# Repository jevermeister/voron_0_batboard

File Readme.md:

# Batboard

The batboard is a passive tool board mounting on the back of the MiniAB pancake 
stepper of the Voron 0.1. The board solidly mounts with 20mm brass standoffs to the 
back of the mini after burner mounting screws and provides JST PH connectors 
(2mm pitch) for the two part cooling fans, the hotend fan, a 4-pin thermistor, 
two switches (for example the X endstop + a klicky probe) as well as the stepper and a chamber thermistor. 
The heater output is provided as a 2x1 Molex Microfit connector and all terminals 
are terminated onto a 2x9 Microfit.

# BOM

For the PCB:
- 1x Molex 43045-1800 (Microfit 2x9) 
- 1x Molex 43045-0200 (Microfit 2x1)
- 3x JST PH 2 Pin, B2B-PH-K-S(LF)(SN)
- 3x JST PH 3 Pin, B3B-PH-K-S(LF)(SN)
- 2x JST PH 4 Pin, B4B-PH-K-S(LF)(SN)
- MF58 3950 thermistor

And the appropriate connectors for your cable loom...

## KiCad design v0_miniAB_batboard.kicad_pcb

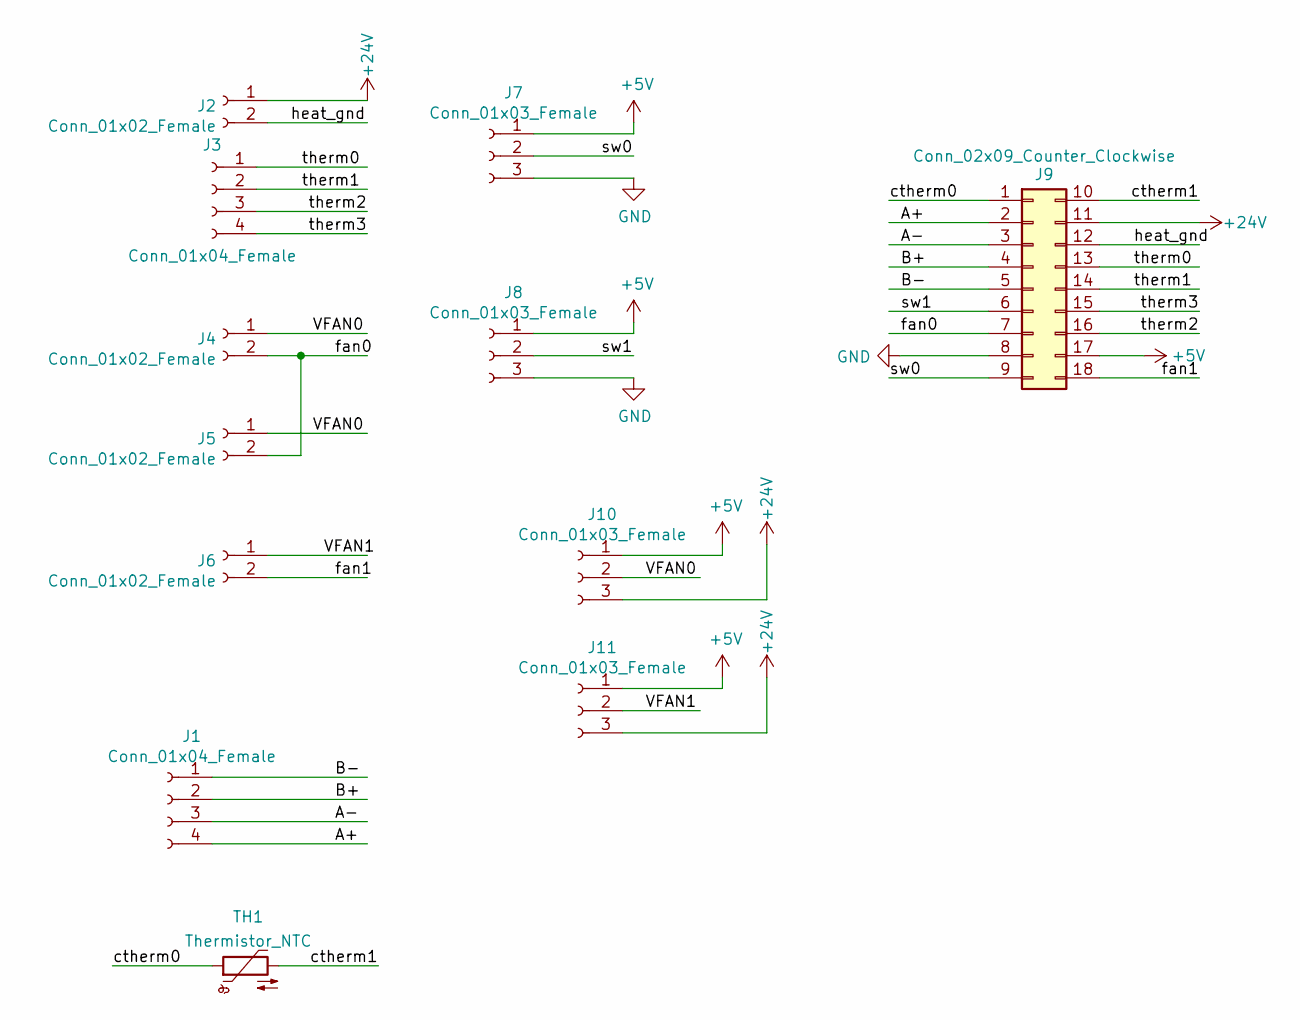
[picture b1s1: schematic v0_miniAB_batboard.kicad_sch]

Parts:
J1, J3: Conn_01x04_Female; JST_PH_B4B-PH-K_1x04_P2.00mm_Vertical
J2: Conn_01x02_Female; Molex_Micro-Fit_3.0_43045-0200_2x01_P3.00mm_Horizontal
J4, J5, J6: Conn_01x02_Female; JST_PH_B2B-PH-K_1x02_P2.00mm_Vertical
J7, J8: Conn_01x03_Female; JST_PH_B3B-PH-K_1x03_P2.00mm_Vertical
J9: Conn_02x09_Counter_Clockwise; Molex_Micro-Fit_3.0_43045-1800_2x09_P3.00mm_Horizontal
J10, J11: Conn_01x03_Female; SolderJumper-3_P1.3mm_Bridged12_RoundedPad1.0x1.5mm_NumberL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
TH1: Thermistor_NTC; R_Axial_DIN0204_L3.6mm_D1.6mm_P7.62mm_Horizontal

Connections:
+5V: J7.1, J8.1, J9.17, J10.1, J11.1
+24V: J2.1, J9.11, J10.3, J11.3
/A+: J1.4, J9.2
/A-: J1.3, J9.3
/B+: J1.2, J9.4
/B-: J1.1, J9.5
/VFAN0: J4.1, J5.1, J10.2
/VFAN1: J6.1, J11.2
/ctherm0: J9.1, TH1.1
/ctherm1: J9.10, TH1.2
/fan0: J4.2, J5.2, J9.7
/fan1: J6.2, J9.18
/heat_gnd: J2.2, J9.12
/sw0: J7.2, J9.9
/sw1: J8.2, J9.6
/therm0: J3.1, J9.13
/therm1: J3.2, J9.14
/therm2: J3.3, J9.16
/therm3: J3.4, J9.15
GND: J7.3, J8.3, J9.8

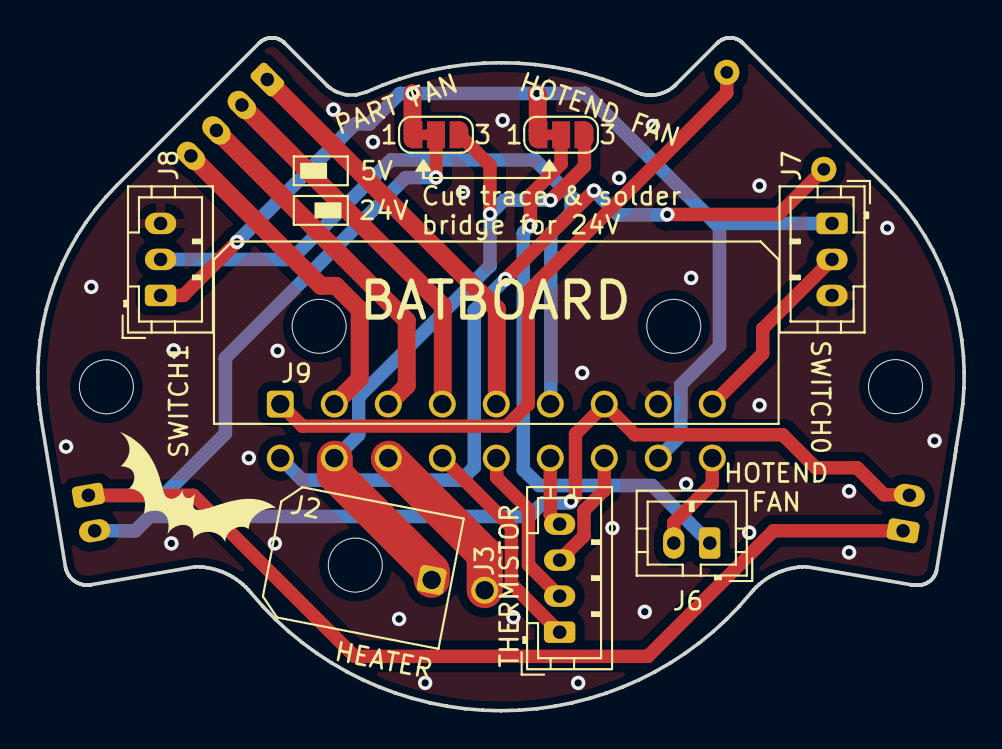
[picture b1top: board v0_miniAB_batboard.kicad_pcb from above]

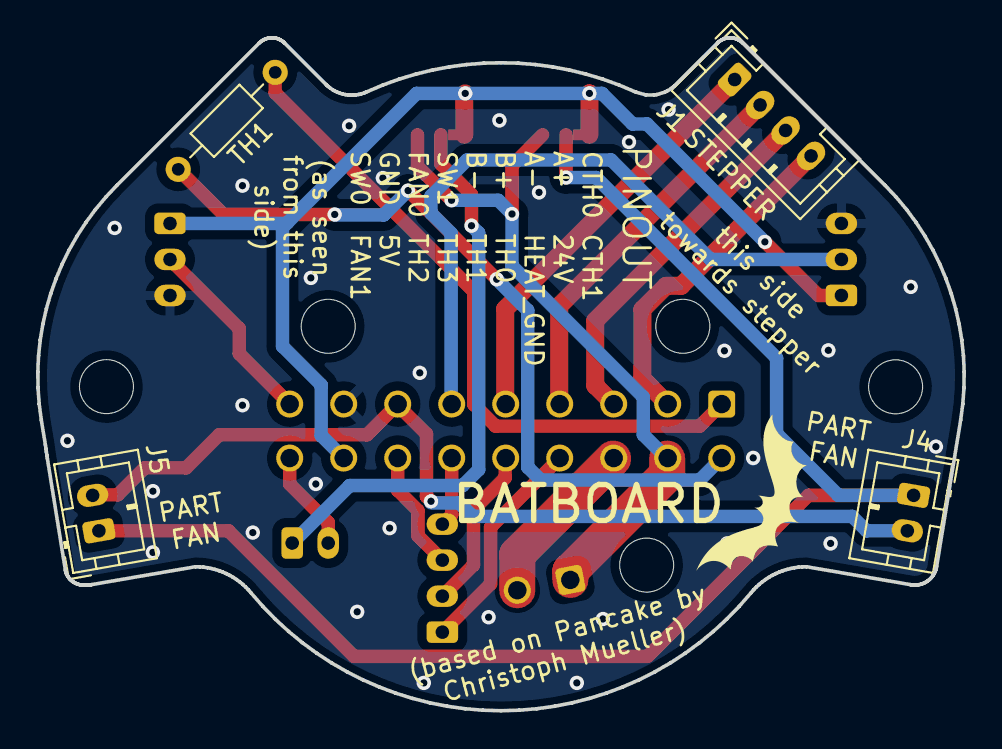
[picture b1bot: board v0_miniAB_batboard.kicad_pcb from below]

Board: 2 copper layers, 51.5 x 37.4 mm, 14 parts (5 on the bottom side), 20 nets.

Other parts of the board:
svg2mod, svg2mod#2: G***; Bat_Logo

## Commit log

2022-01-11 Converted to KiCAD 6.0.0
2022-01-21 First steps of the batboard conversion
2022-01-21 Further connections made
2022-01-21 Fixed track to VFAN1
2022-01-21 Removed mini bat behind connector
    KSS KSSSSSS
2022-01-25 Moved some things, added CT, checked clearance
2022-01-25 Adapted readme for batboard
2022-01-25 Removed unused files
2022-01-25 Renamed files
2022-01-25 Minor adjustments and added Gerber files
